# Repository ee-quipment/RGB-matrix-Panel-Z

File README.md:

# RGB-matrix-Panel-Zero
Libraries to drive LED Matrix panels from the Arduino MKRZero and the Adafruit Feather M0 boards.

### What's here?
All sorts of stuff. Graphics drivers, adapter schematics, and PCBs.

There are two libraries, a forked Adafruit/RGB-matrix-Panel to work with Feather M0 boards which
will drive panels in 12 bit color, and a simpler, faster driver which works with both the Arduino
and Feather boards but is limited to 8 colors.

### Forked Adafruit RGBmatrixPanel Library
- Adds support for Feather M0 boards.
- Drives 16 and 32 row panels. See LEDpanel library for 64 row panels.
- All changes are via #ifdef ARDUINO_SAMD_FEATHER_M0.
- No change to the interface. Pin assignments in the constructor are ignored.
- Adds an interrupt handler which pushes pixels directly out the hardware I/O port.

This library directly replaces the RGBmatrixPanel.cpp from the Adafruit library. It is
plug-and-play, no other changes are required. Any existing code and all examples at
https://github.com/adafruit/RGB-matrix-Panel/tree/master/examples will now run unmodified
on your Feather M0.

### LEDpanel library
This library supports both Arduino MKRZero and Feather M0 boards. It is strictly a driver that
takes a pointer to a frame buffer and drives the display. Each pixel is one of 8 colors stored
as the lowest 3 bits in a byte. ex: 00000BGR. The total display buffer size is (width * height) bytes.
Panels with 16, 32, and 64 rows are supported. A 32 x 32 panel can be refreshed at over 2 KHz.

### Pinouts and connections
The pinout is fixed. The SPI and I2C ports are free and available. On the Feather M0 the LED_BUILTIN
port is used. Don't try to control the LED or it will affect the panel display.

There are schematics for both boards with a bill of materials and Digikey part numbers for connectors
if you wish to build an adapter on a proto board, or you can order a PCB from Oshpark.com. Eagle CAD
files are also supplied if you want to do some customization.

The adapter board can be confiured to directly plug into the back of the panel, or to connect to a
ribbon cable. You can also connect a power connector to the adapter board making
the processor/panel combination completely self-contained.

<a href="https://oshpark.com/shared_projects/7h8QPZrN">Oshpark FeatherWing</a>

<a href="https://oshpark.com/shared_projects/TkdU88Pn">Oshpark MKR Shield</a>

<p align="center"> 
  
<p align="center"> 
  
<p align="center"> 

There are more pictures in the /images directory.

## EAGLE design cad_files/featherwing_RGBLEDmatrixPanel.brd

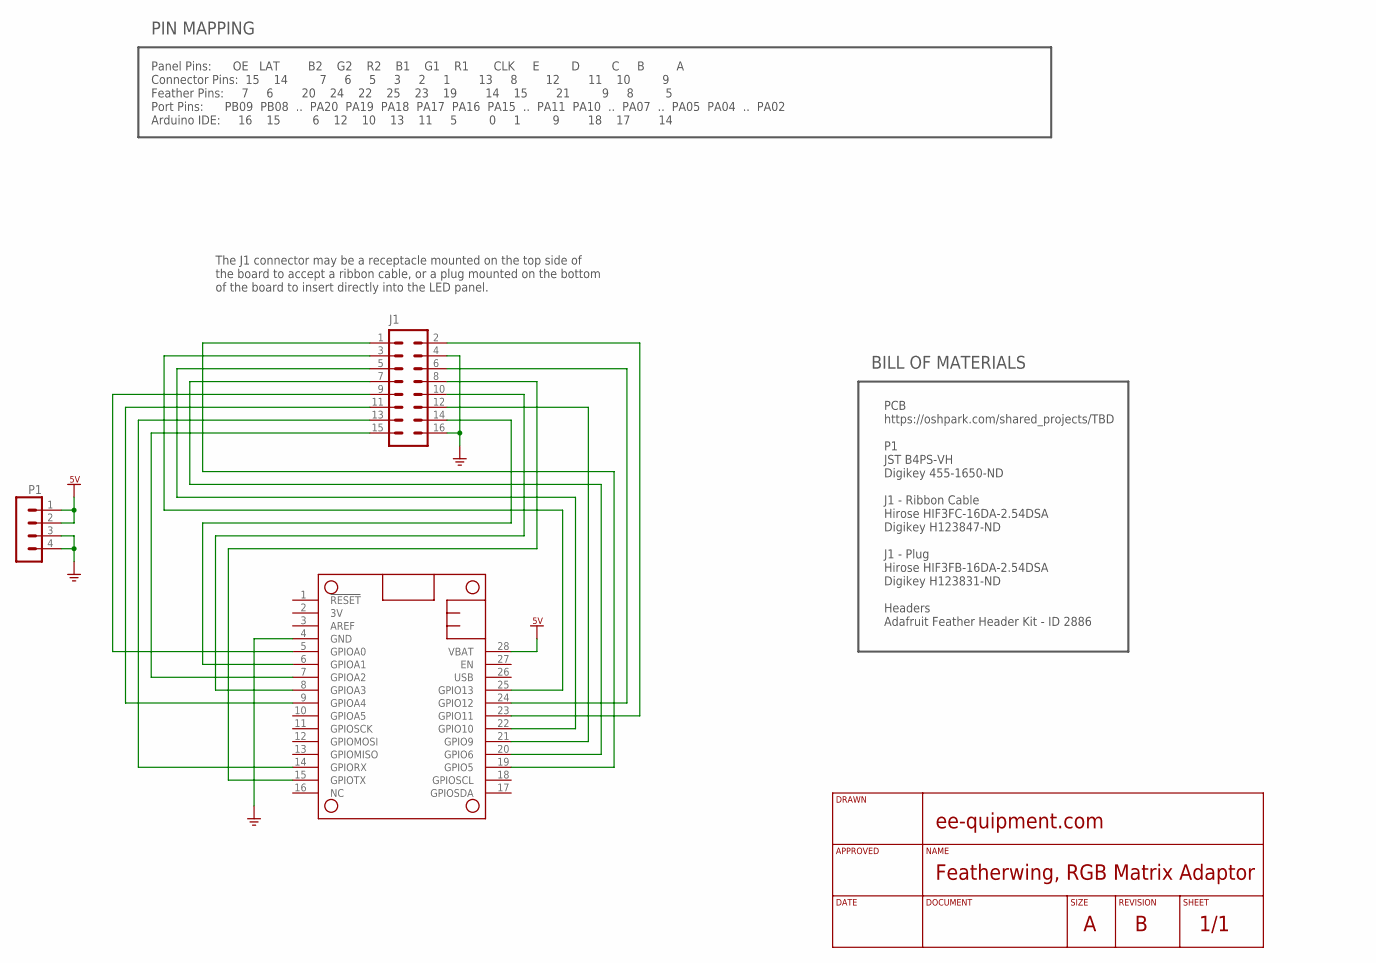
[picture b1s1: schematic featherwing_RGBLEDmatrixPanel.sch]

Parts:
J1: HDR_16
MS1: MICROSHIELD
P1: JST_B4P-VHRA; JST_B4PS-VH

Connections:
5V: MS1.28 (VBAT), P1.1, P1.2
GND: J1.4, J1.16, MS1.4 (GND), P1.3, P1.4
unnamed: J1.9, MS1.5 (GPIOA0)
unnamed: J1.14, MS1.6 (GPIOA1)
unnamed: J1.15, MS1.7 (GPIOA2)
unnamed: J1.10, MS1.8 (GPIOA3)
unnamed: J1.11, MS1.9 (GPIOA4)
unnamed: J1.13, MS1.14 (GPIORX)
unnamed: J1.1, MS1.19 (GPIO5)
unnamed: J1.7, MS1.20 (GPIO6)
unnamed: J1.12, MS1.21 (GPIO9)
unnamed: J1.5, MS1.22 (GPIO10)
unnamed: J1.2, MS1.23 (GPIO11)
unnamed: J1.6, MS1.24 (GPIO12)
unnamed: J1.3, MS1.25 (GPIO13)
unnamed: J1.8, MS1.15 (GPIOTX)

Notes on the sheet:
The J1 connector may be a receptacle mounted on the top side of the board to accept a ribbon cable, or a plug mounted on the bottom of the board to insert directly into the LED panel.
PCB https://oshpark.com/shared_projects/TBD P1 JST B4PS-VH Digikey 455-1650-ND J1 - Ribbon Cable Hirose HIF3FC-16DA-2.54DSA Digikey H123847-ND J1 - Plug Hirose HIF3FB-16DA-2.54DSA Digikey H123831-ND Headers Adafruit Feather Header Kit - ID 2886
BILL OF MATERIALS
Panel Pins: OE LAT B2 G2 R2 B1 G1 R1 CLK E D C B A Connector Pins: 15 14 7 6 5 3 2 1 13 8 12 11 10 9 Feather Pins: 7 6 20 24 22 25 23 19 14 15 21 9 8 5 Port Pins: PB09 PB08 .. PA20 PA19 PA18 PA17 PA16 PA15 .. PA11 PA10 .. PA07 .. PA05 PA04 .. PA02 Arduino IDE: 16 15 6 12 10 13 11 5 0 1 9 18 17 14
PIN MAPPING

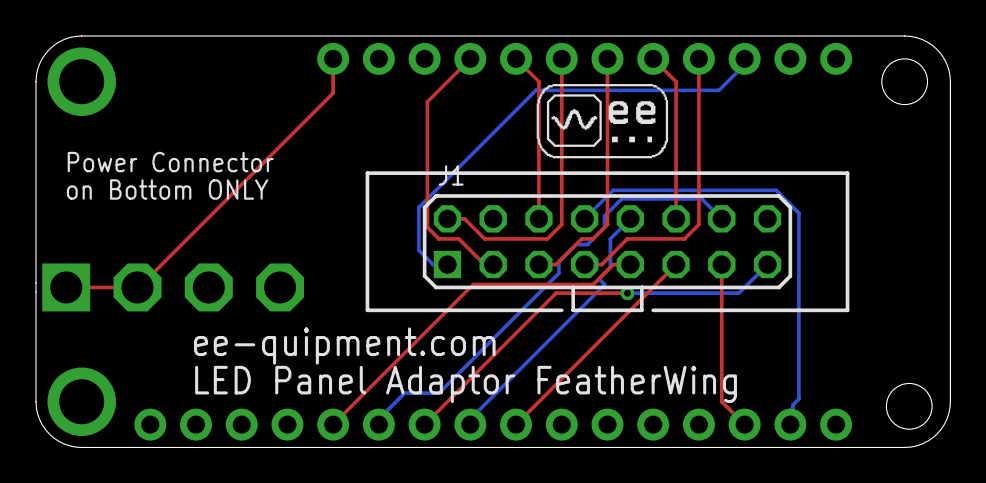
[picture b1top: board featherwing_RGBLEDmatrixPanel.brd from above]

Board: 2 copper layers, 50.8 x 22.9 mm, 5 parts (1 on the bottom side), 16 nets.

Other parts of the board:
U$2: EE_QUIPMENT_LOGO_128X128
U$4: FORMAT_A_L_EE-QUIPMENT

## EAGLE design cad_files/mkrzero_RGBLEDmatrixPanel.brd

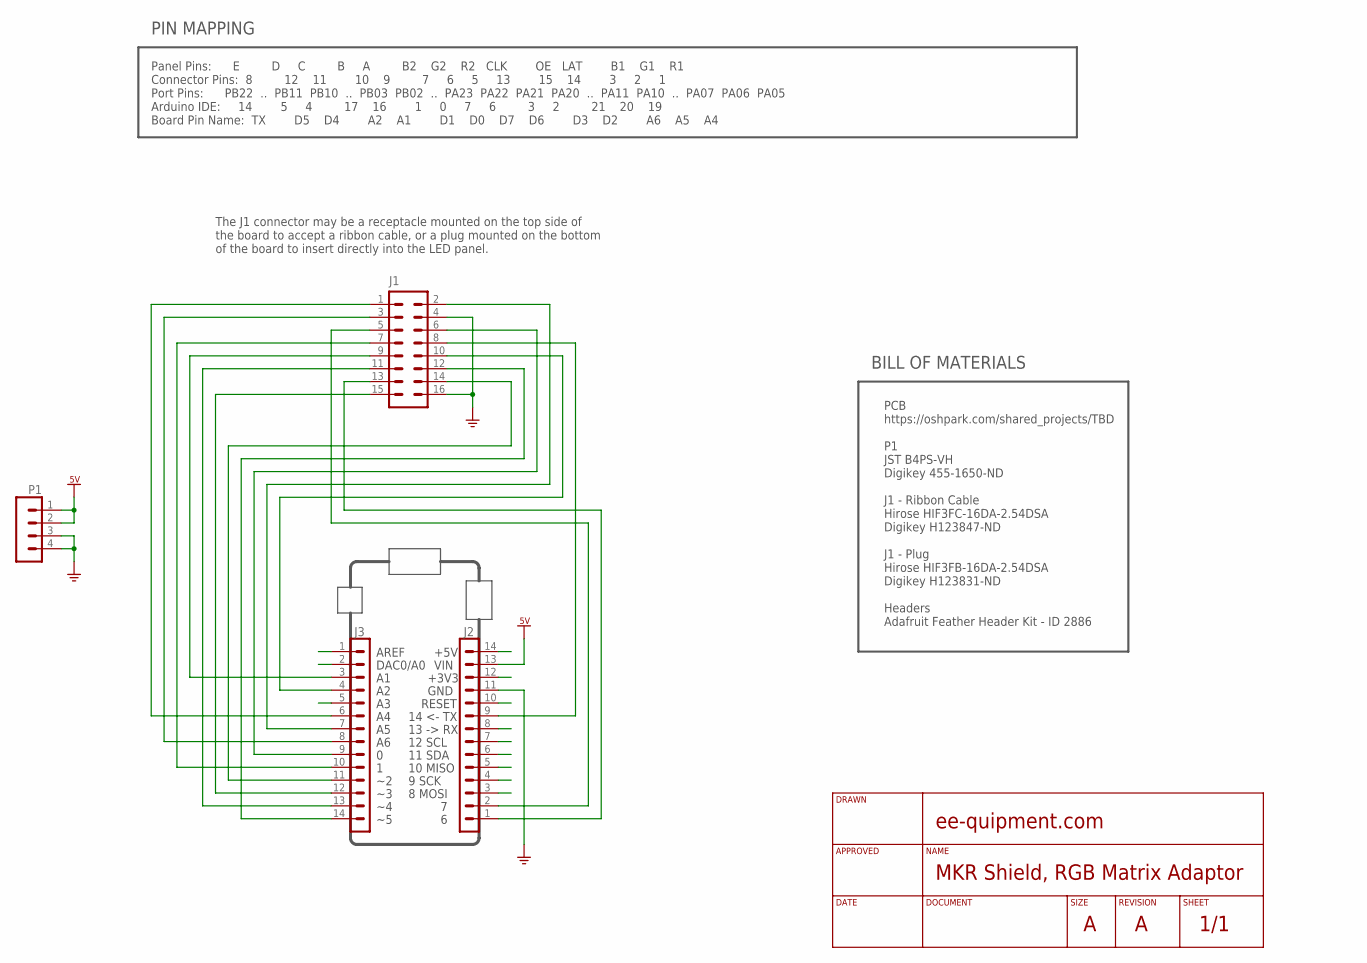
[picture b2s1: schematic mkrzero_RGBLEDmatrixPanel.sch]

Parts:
J1: HDR_16
J2, J3: DNP; STRIP-14-MODULI-A11
P1: JST_B4P-VHRA; JST_B4PS-VH

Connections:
5V: J2.13, P1.1, P1.2
+3V3: J2.12
+5V: J2.14
GND: J1.4, J1.16, J2.11, P1.3, P1.4
PA02_AIN0: J3.2
PA03_VREFA: J3.1
PA04_AIN4: J3.5
PA05_AIN5: J1.1, J3.6
PA06_AIN6: J1.2, J3.7
PA07_AIN7: J1.3, J3.8
PA08_S0_I2C_SDA: J2.6
PA09_S0_I2C_SCL: J2.7
PA10_TCC0-W2: J1.14, J3.11
PA11_TCC0-W3: J1.15, J3.12
PA16_S1_MOSI: J2.3
PA17_S1_SCK: J2.4
PA19_S1_MISO: J2.5
PA20_TCC0-W6: J1.13, J2.1
PA21_TCC0-W7: J1.5, J2.2
PA22_TC4-W0: J1.6, J3.9
PA23_TC4-W1: J1.7, J3.10
PB02_AIN10: J1.9, J3.3
PB03_AIN11: J1.10, J3.4
PB10_TCC0-W4: J1.11, J3.13
PB11_TCC0-W5: J1.12, J3.14
PB22_S5_TX: J1.8, J2.9
PB23_S5_RX: J2.8
RESET#: J2.10

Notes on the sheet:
The J1 connector may be a receptacle mounted on the top side of the board to accept a ribbon cable, or a plug mounted on the bottom of the board to insert directly into the LED panel.
PCB https://oshpark.com/shared_projects/TBD P1 JST B4PS-VH Digikey 455-1650-ND J1 - Ribbon Cable Hirose HIF3FC-16DA-2.54DSA Digikey H123847-ND J1 - Plug Hirose HIF3FB-16DA-2.54DSA Digikey H123831-ND Headers Adafruit Feather Header Kit - ID 2886
BILL OF MATERIALS
Panel Pins: E D C B A B2 G2 R2 CLK OE LAT B1 G1 R1 Connector Pins: 8 12 11 10 9 7 6 5 13 15 14 3 2 1 Port Pins: PB22 .. PB11 PB10 .. PB03 PB02 .. PA23 PA22 PA21 PA20 .. PA11 PA10 .. PA07 PA06 PA05 Arduino IDE: 14 5 4 17 16 1 0 7 6 3 2 21 20 19 Board Pin Name: TX D5 D4 A2 A1 D1 D0 D7 D6 D3 D2 A6 A5 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
PIN MAPPING
14 <- TX
13 -> RX
12 SCL
RESET
11 SDA
8 MOSI
9 SCK
10 MISO
AREF
DAC0/A0
+5V
VIN
+3V3
GND

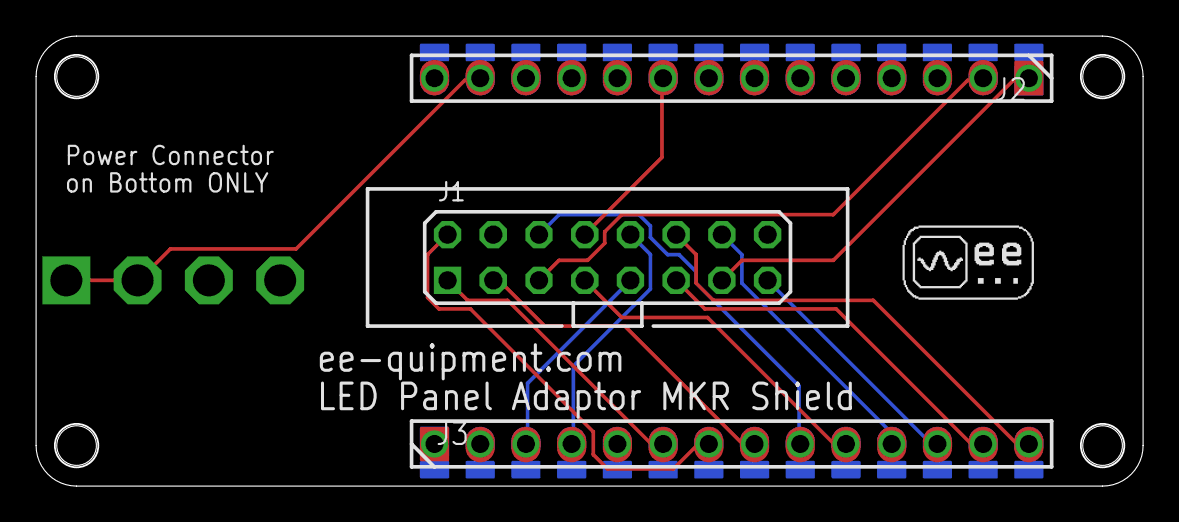
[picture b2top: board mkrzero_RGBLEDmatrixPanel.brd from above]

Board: 2 copper layers, 61.4 x 24.9 mm, 10 parts (1 on the bottom side), 16 nets.

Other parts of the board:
U$2: EE_QUIPMENT_LOGO_128X128
U$4: FORMAT_A_L_EE-QUIPMENT
U$5, U$6, U$7, U$8: MH_RND_F_2.2MM_NM

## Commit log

2018-05-14 readme
2018-05-16 rev A
2018-05-16 rev A Schematic
2018-05-16 source
2018-05-16 image
2018-05-16 images
2018-05-16 connection diagram
2018-06-01 pdf schematics, eagle sch and brf files
2018-06-01 pdf schematics, eagle sch and brd files
2018-06-01 license
2018-06-01 Feather pinout
2018-09-10 Move example sketch to appropriately named folder
    The Arduino IDE requires the sketch folder name to match the filename of the primary sketch file. This change causes the example sketch to be accessible via the Arduino IDE's File > Examples > LIBRAR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
    Reference:
    https://github.com/arduino/Arduino/wiki/Arduino-IDE-1.5:-Library-specification#library-examples
